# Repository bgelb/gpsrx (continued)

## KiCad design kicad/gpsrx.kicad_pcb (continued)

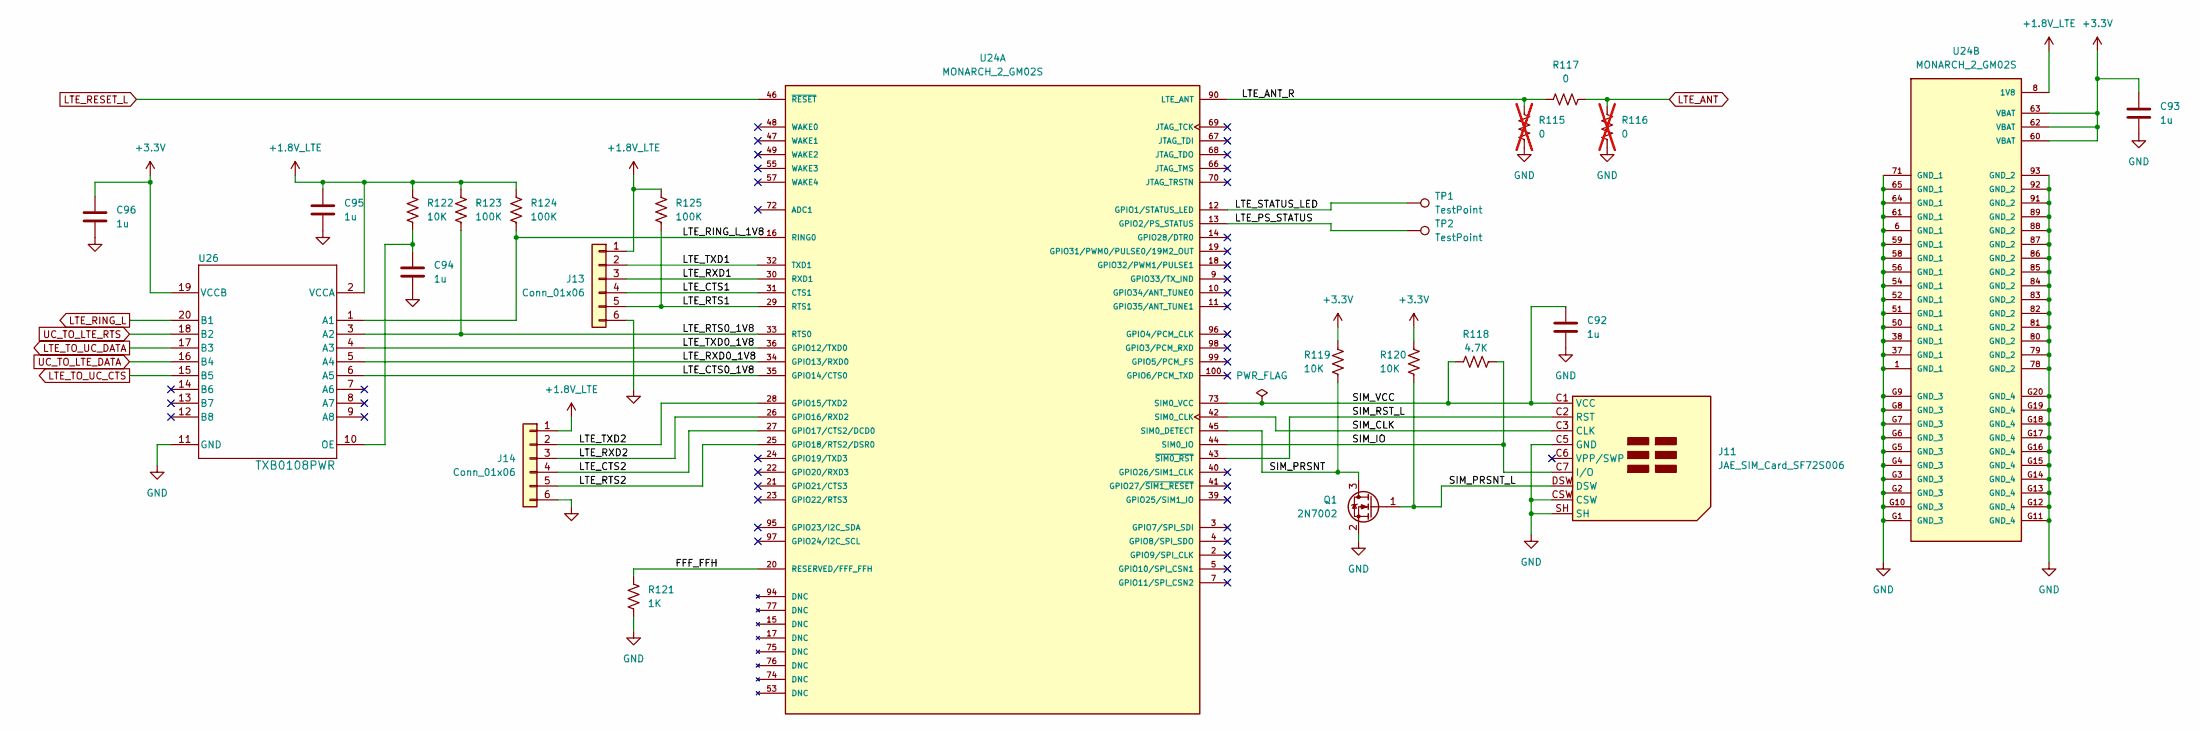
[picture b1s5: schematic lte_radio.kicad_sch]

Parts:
C92, C93, C94, C95, C96: 1u; C_0603_1608Metric_Pad1.08x0.95mm_HandSolder
J11: JAE_SIM_Card_SF72S006
J13, J14: Conn_01x06; PinSocket_1x06_P2.54mm_Vertical
Q1: 2N7002; SOT-23
R115, R116: 0; R_0603_1608Metric_Pad0.98x0.95mm_HandSolder; not fitted
R117: 0; R_0603_1608Metric_Pad0.98x0.95mm_HandSolder
R118: 4.7K; R_0603_1608Metric_Pad0.98x0.95mm_HandSolder
R119, R120, R122: 10K; R_0603_1608Metric_Pad0.98x0.95mm_HandSolder
R121: 1K; R_0603_1608Metric_Pad0.98x0.95mm_HandSolder
R123, R124, R125: 100K; R_0603_1608Metric_Pad0.98x0.95mm_HandSolder
TP1, TP2: TestPoint; TestPoint_Pad_D1.0mm
U24: MONARCH_2_GM02S; XCVR_MONARCH_2_GM02S; PARTREV 11
U26: TXB0108PWR; PW0020A_N

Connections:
/LTE Radio/FFF_FFH: R121.1, U24.20 (RESERVED/FFF_FFH)
/LTE Radio/LTE_ANT_R: R115.1, R117.1, U24.90 (LTE_ANT)
/LTE Radio/LTE_CTS0_1V8: U24.35 (GPIO14/CTS0), U26.6 (A5)
/LTE Radio/LTE_CTS1: J13.4, U24.31 (CTS1)
/LTE Radio/LTE_CTS2: J14.4, U24.27 (GPIO17/CTS2/DCD0)
/LTE Radio/LTE_PS_STATUS: TP2.1, U24.13 (GPIO2/PS_STATUS)
/LTE Radio/LTE_RING_L_1V8: R124.2, U24.16 (RING0), U26.1 (A1)
/LTE Radio/LTE_RTS0_1V8: R123.2, U24.33 (RTS0), U26.3 (A2)
/LTE Radio/LTE_RTS1: J13.5, R125.2, U24.29 (RTS1)
/LTE Radio/LTE_RTS2: J14.5, U24.25 (GPIO18/RTS2/DSR0)
/LTE Radio/LTE_RXD0_1V8: U24.34 (GPIO13/RXD0), U26.5 (A4)
/LTE Radio/LTE_RXD1: J13.3, U24.30 (RXD1)
/LTE Radio/LTE_RXD2: J14.3, U24.26 (GPIO16/RXD2)
/LTE Radio/LTE_STATUS_LED: TP1.1, U24.12 (GPIO1/STATUS_LED)
/LTE Radio/LTE_TXD0_1V8: U24.36 (GPIO12/TXD0), U26.4 (A3)
/LTE Radio/LTE_TXD1: J13.2, U24.32 (TXD1)
/LTE Radio/LTE_TXD2: J14.2, U24.28 (GPIO15/TXD2)
/LTE Radio/SIM_CLK: J11.C3 (CLK), U24.42 (SIM0_CLK)
/LTE Radio/SIM_IO: J11.C7 (I/O), R118.2, U24.44 (SIM0_IO)
/LTE Radio/SIM_PRSNT: Q1.3 (D), R119.2, U24.45 (SIM0_DETECT)
/LTE Radio/SIM_PRSNT_L: J11.DSW, Q1.1 (G), R120.2
/LTE Radio/SIM_RST_L: J11.C2 (RST), U24.43 (~SIM0_RST)
/LTE Radio/SIM_VCC: C92.1, J11.C1 (VCC), R118.1, U24.73 (SIM0_VCC)
GND: C92.2, C93.2, C94.2, C95.2, C96.2, J11.C5 (GND), J11.CSW, J11.SH, J13.6, J14.6, Q1.2 (S), R115.2, R116.2, R121.2, U24.1 (GND_1), U24.6 (GND_1), U24.37 (GND_1), U24.38 (GND_1), U24.50 (GND_1), U24.51 (GND_1), U24.52 (GND_1), U24.54 (GND_1), U24.56 (GND_1), U24.58 (GND_1), U24.59 (GND_1), U24.61 (GND_1), U24.64 (GND_1), U24.65 (GND_1), U24.71 (GND_1), U24.78 (GND_2), U24.79 (GND_2), U24.80 (GND_2), U24.81 (GND_2), U24.82 (GND_2), U24.83 (GND_2), U24.84 (GND_2), U24.85 (GND_2), U24.86 (GND_2), U24.87 (GND_2), U24.88 (GND_2), U24.89 (GND_2), U24.91 (GND_2), U24.92 (GND_2), U24.93 (GND_2), U24.G1 (GND_3), U24.G2 (GND_3), U24.G3 (GND_3), U24.G4 (GND_3), U24.G5 (GND_3), U24.G6 (GND_3), U24.G7 (GND_3), U24.G8 (GND_3), U24.G9 (GND_3), U24.G10 (GND_3), U24.G11 (GND_4), U24.G12 (GND_4), U24.G13 (GND_4), U24.G14 (GND_4), U24.G15 (GND_4), U24.G16 (GND_4), U24.G17 (GND_4), U24.G18 (GND_4), U24.G19 (GND_4), U24.G20 (GND_4), U26.11 (GND); also elsewhere on the board
LTE_ANT: R116.1, R117.2; also elsewhere on the board
LTE_RESET_L: U24.46 (~RESET); also elsewhere on the board
LTE_RING_L: U26.20 (B1); also elsewhere on the board
LTE_TO_UC_CTS: U26.15 (B5); also elsewhere on the board
LTE_TO_UC_DATA: U26.17 (B3); also elsewhere on the board
unnamed: C94.1, R122.2, U26.10 (OE)
UC_TO_LTE_DATA: U26.16 (B4); also elsewhere on the board
UC_TO_LTE_RTS: U26.18 (B2); also elsewhere on the board

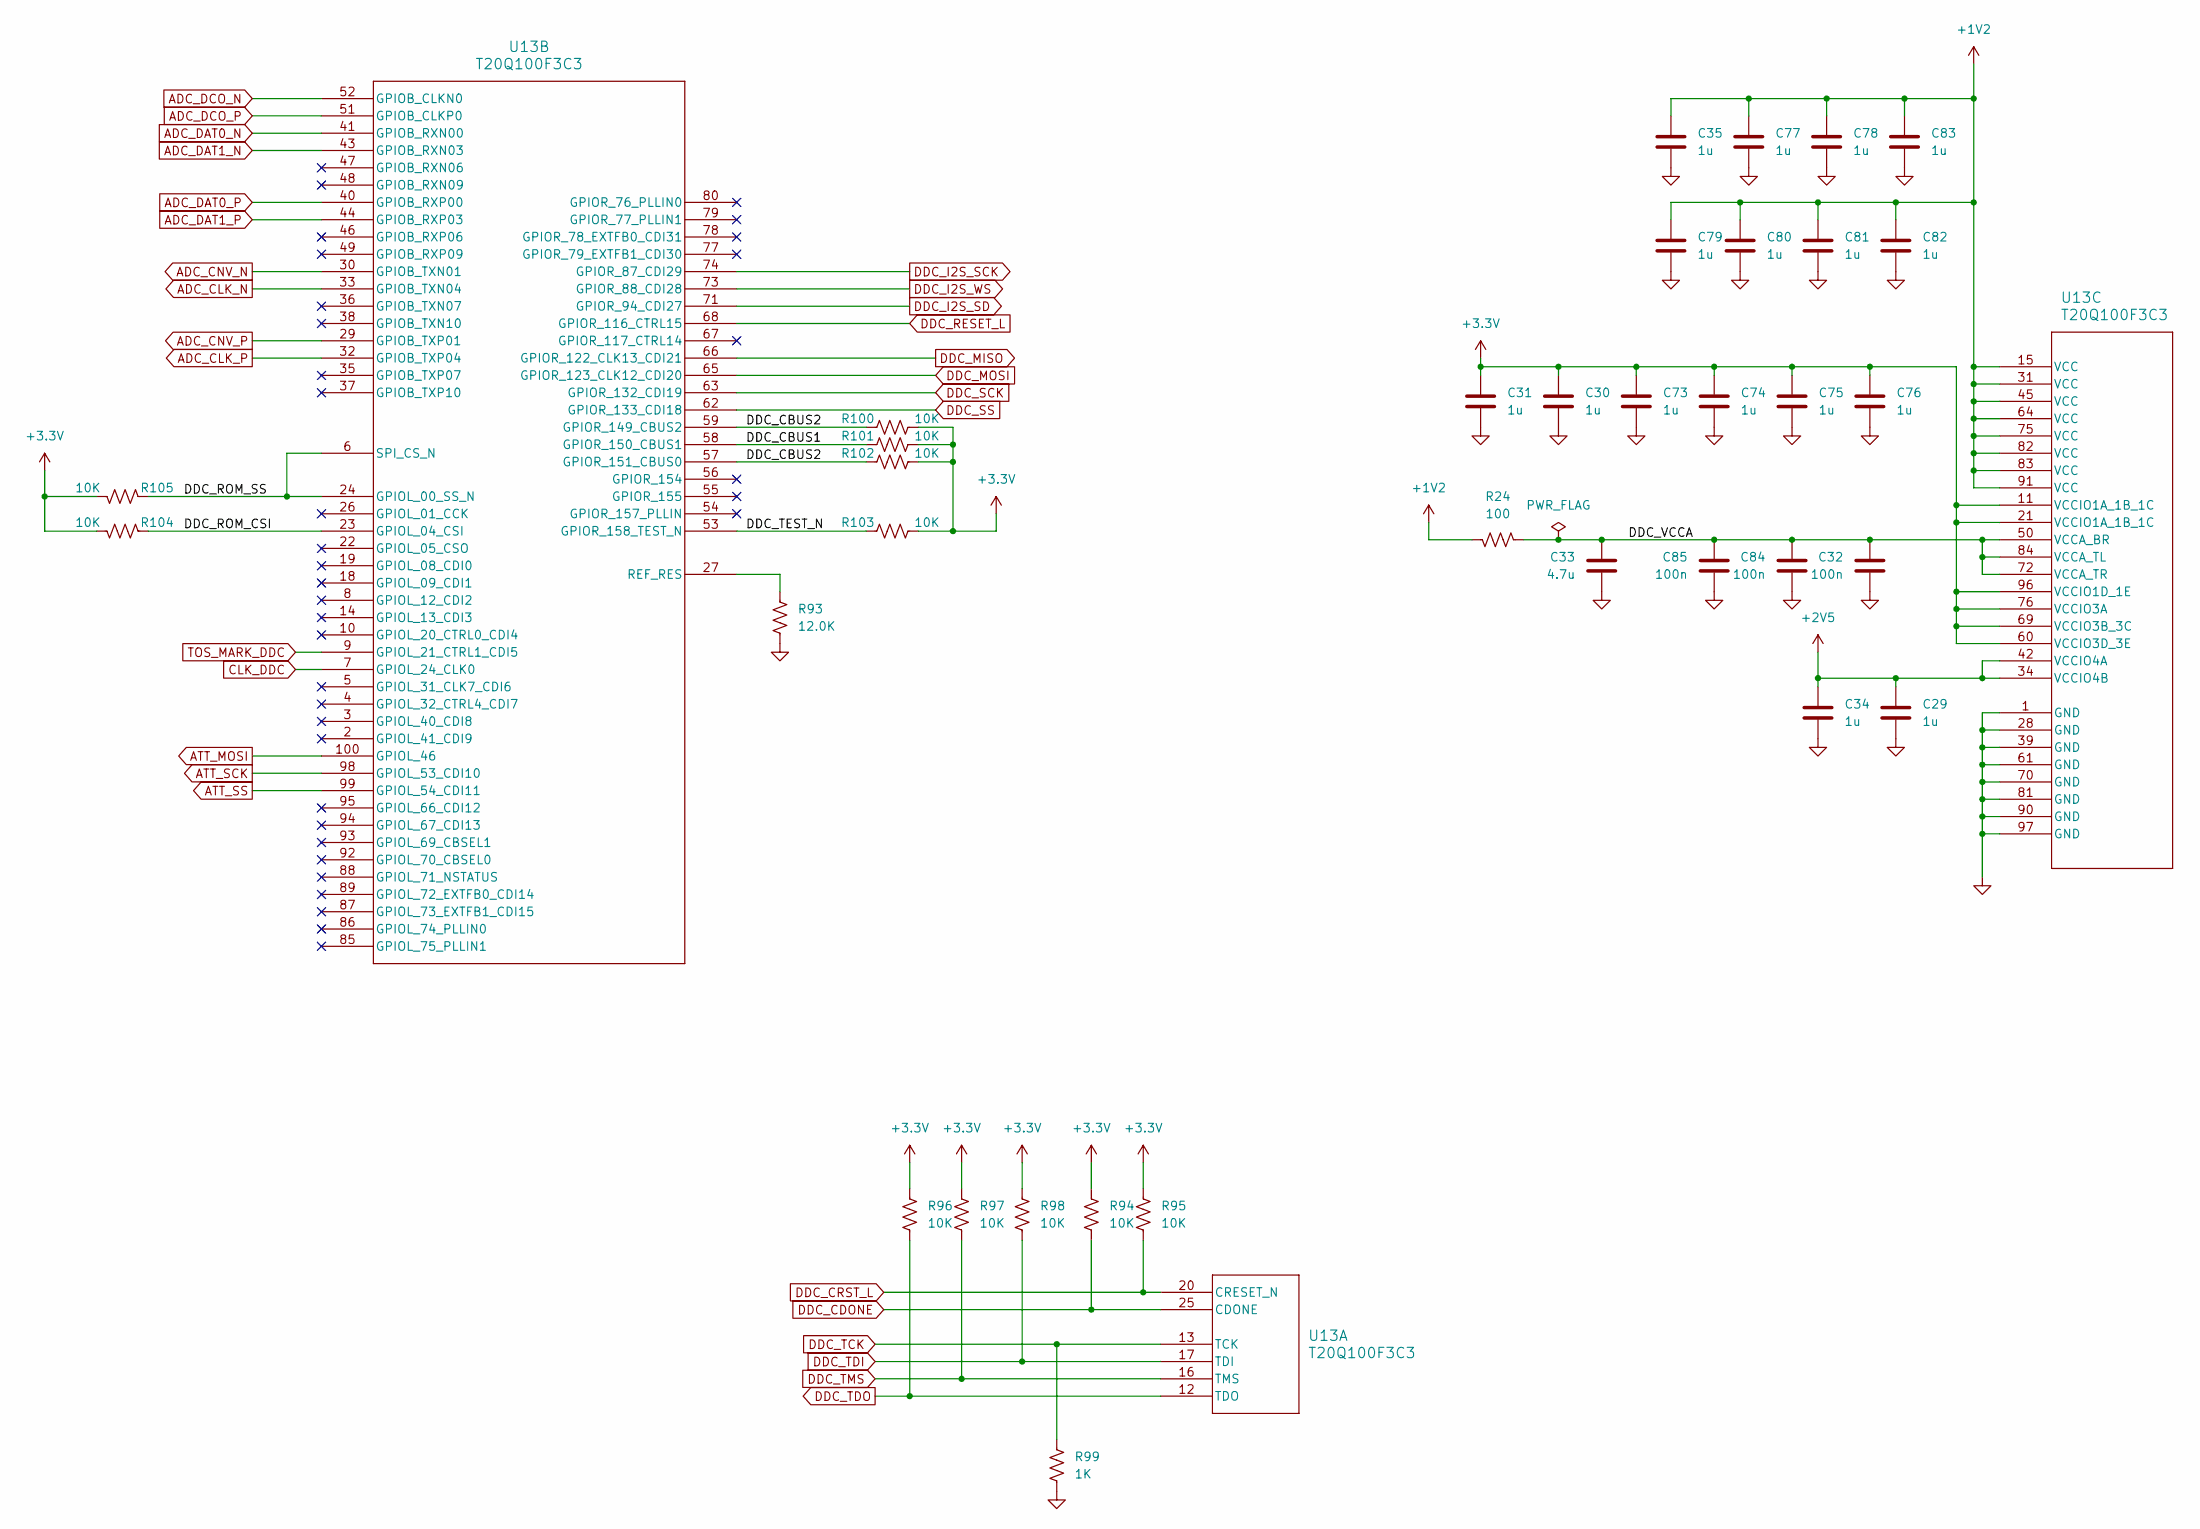
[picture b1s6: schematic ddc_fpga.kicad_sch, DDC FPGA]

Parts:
C29, C30, C31, C34, C35, C73, C74, C75, C76, C77, C78, C79, C80, C81, C82, C83: 1u; C_0603_1608Metric_Pad1.08x0.95mm_HandSolder
C32, C84, C85: 100n; C_0603_1608Metric_Pad1.08x0.95mm_HandSolder
C33: 4.7u; C_0603_1608Metric_Pad1.08x0.95mm_HandSolder
R24: 100; R_0603_1608Metric_Pad0.98x0.95mm_HandSolder
R93: 12.0K; R_0603_1608Metric_Pad0.98x0.95mm_HandSolder
R94, R95, R96, R97, R98, R100, R101, R102, R103, R104, R105: 10K; R_0603_1608Metric_Pad0.98x0.95mm_HandSolder
R99: 1K; R_0603_1608Metric_Pad0.98x0.95mm_HandSolder
U13: T20Q100F3C3; LQFP100_TRION_EFI

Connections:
+1V2: C35.1, C77.1, C78.1, C79.1, C80.1, C81.1, C82.1, C83.1, R24.2, U13.15 (VCC), U13.31 (VCC), U13.45 (VCC), U13.64 (VCC), U13.75 (VCC), U13.82 (VCC), U13.83 (VCC), U13.91 (VCC); also elsewhere on the board
+2V5: C29.1, C34.1, U13.34 (VCCIO4B), U13.42 (VCCIO4A); also elsewhere on the board
/DDC FPGA/DDC_CBUS1: R101.1, U13.58 (GPIOR_150_CBUS1)
/DDC FPGA/DDC_CBUS2: R100.1, R102.1, U13.57 (GPIOR_151_CBUS0), U13.59 (GPIOR_149_CBUS2)
/DDC FPGA/DDC_ROM_CSI: R104.1, U13.23 (GPIOL_04_CSI)
/DDC FPGA/DDC_ROM_SS: R105.1, U13.6 (SPI_CS_N), U13.24 (GPIOL_00_SS_N)
/DDC FPGA/DDC_TEST_N: R103.1, U13.53 (GPIOR_158_TEST_N)
/DDC FPGA/DDC_VCCA: C32.1, C33.1, C84.1, C85.1, R24.1, U13.50 (VCCA_BR), U13.72 (VCCA_TR), U13.84 (VCCA_TL)
ADC_CLK_N: U13.33 (GPIOB_TXN04); also elsewhere on the board
ADC_CLK_P: U13.32 (GPIOB_TXP04); also elsewhere on the board
ADC_CNV_N: U13.30 (GPIOB_TXN01); also elsewhere on the board
ADC_CNV_P: U13.29 (GPIOB_TXP01); also elsewhere on the board
ADC_DAT0_N: U13.41 (GPIOB_RXN00); also elsewhere on the board
ADC_DAT0_P: U13.40 (GPIOB_RXP00); also elsewhere on the board
ADC_DAT1_N: U13.43 (GPIOB_RXN03); also elsewhere on the board
ADC_DAT1_P: U13.44 (GPIOB_RXP03); also elsewhere on the board
ADC_DCO_N: U13.52 (GPIOB_CLKN0); also elsewhere on the board
ADC_DCO_P: U13.51 (GPIOB_CLKP0); also elsewhere on the board
ATT_MOSI: U13.100 (GPIOL_46); also elsewhere on the board
ATT_SCK: U13.98 (GPIOL_53_CDI10); also elsewhere on the board
ATT_SS: U13.99 (GPIOL_54_CDI11); also elsewhere on the board
CLK_DDC: U13.7 (GPIOL_24_CLK0); also elsewhere on the board
DDC_CDONE: R94.2, U13.25 (CDONE); also elsewhere on the board
DDC_CRST_L: R95.2, U13.20 (CRESET_N); also elsewhere on the board
DDC_I2S_SCK: U13.74 (GPIOR_87_CDI29); also elsewhere on the board
DDC_I2S_SD: U13.71 (GPIOR_94_CDI27); also elsewhere on the board
DDC_I2S_WS: U13.73 (GPIOR_88_CDI28); also elsewhere on the board
DDC_MISO: U13.66 (GPIOR_122_CLK13_CDI21); also elsewhere on the board
DDC_MOSI: U13.65 (GPIOR_123_CLK12_CDI20); also elsewhere on the board
DDC_RESET_L: U13.68 (GPIOR_116_CTRL15); also elsewhere on the board
DDC_SCK: U13.63 (GPIOR_132_CDI19); also elsewhere on the board
DDC_SS: U13.62 (GPIOR_133_CDI18); also elsewhere on the board
DDC_TCK: R99.1, U13.13 (TCK); also elsewhere on the board
DDC_TDI: R98.2, U13.17 (TDI); also elsewhere on the board
DDC_TDO: R96.2, U13.12 (TDO); also elsewhere on the board
DDC_TMS: R97.2, U13.16 (TMS); also elsewhere on the board
GND: C29.2, C30.2, C31.2, C32.2, C33.2, C34.2, C35.2, C73.2, C74.2, C75.2, C76.2, C77.2, C78.2, C79.2, C80.2, C81.2, C82.2, C83.2, C84.2, C85.2, R93.2, R99.2, U13.1 (GND), U13.28 (GND), U13.39 (GND), U13.61 (GND), U13.70 (GND), U13.81 (GND), U13.90 (GND), U13.97 (GND); also elsewhere on the board
unnamed: R93.1, U13.27 (REF_RES)
TOS_MARK_DDC: U13.9 (GPIOL_21_CTRL1_CDI5); also elsewhere on the board

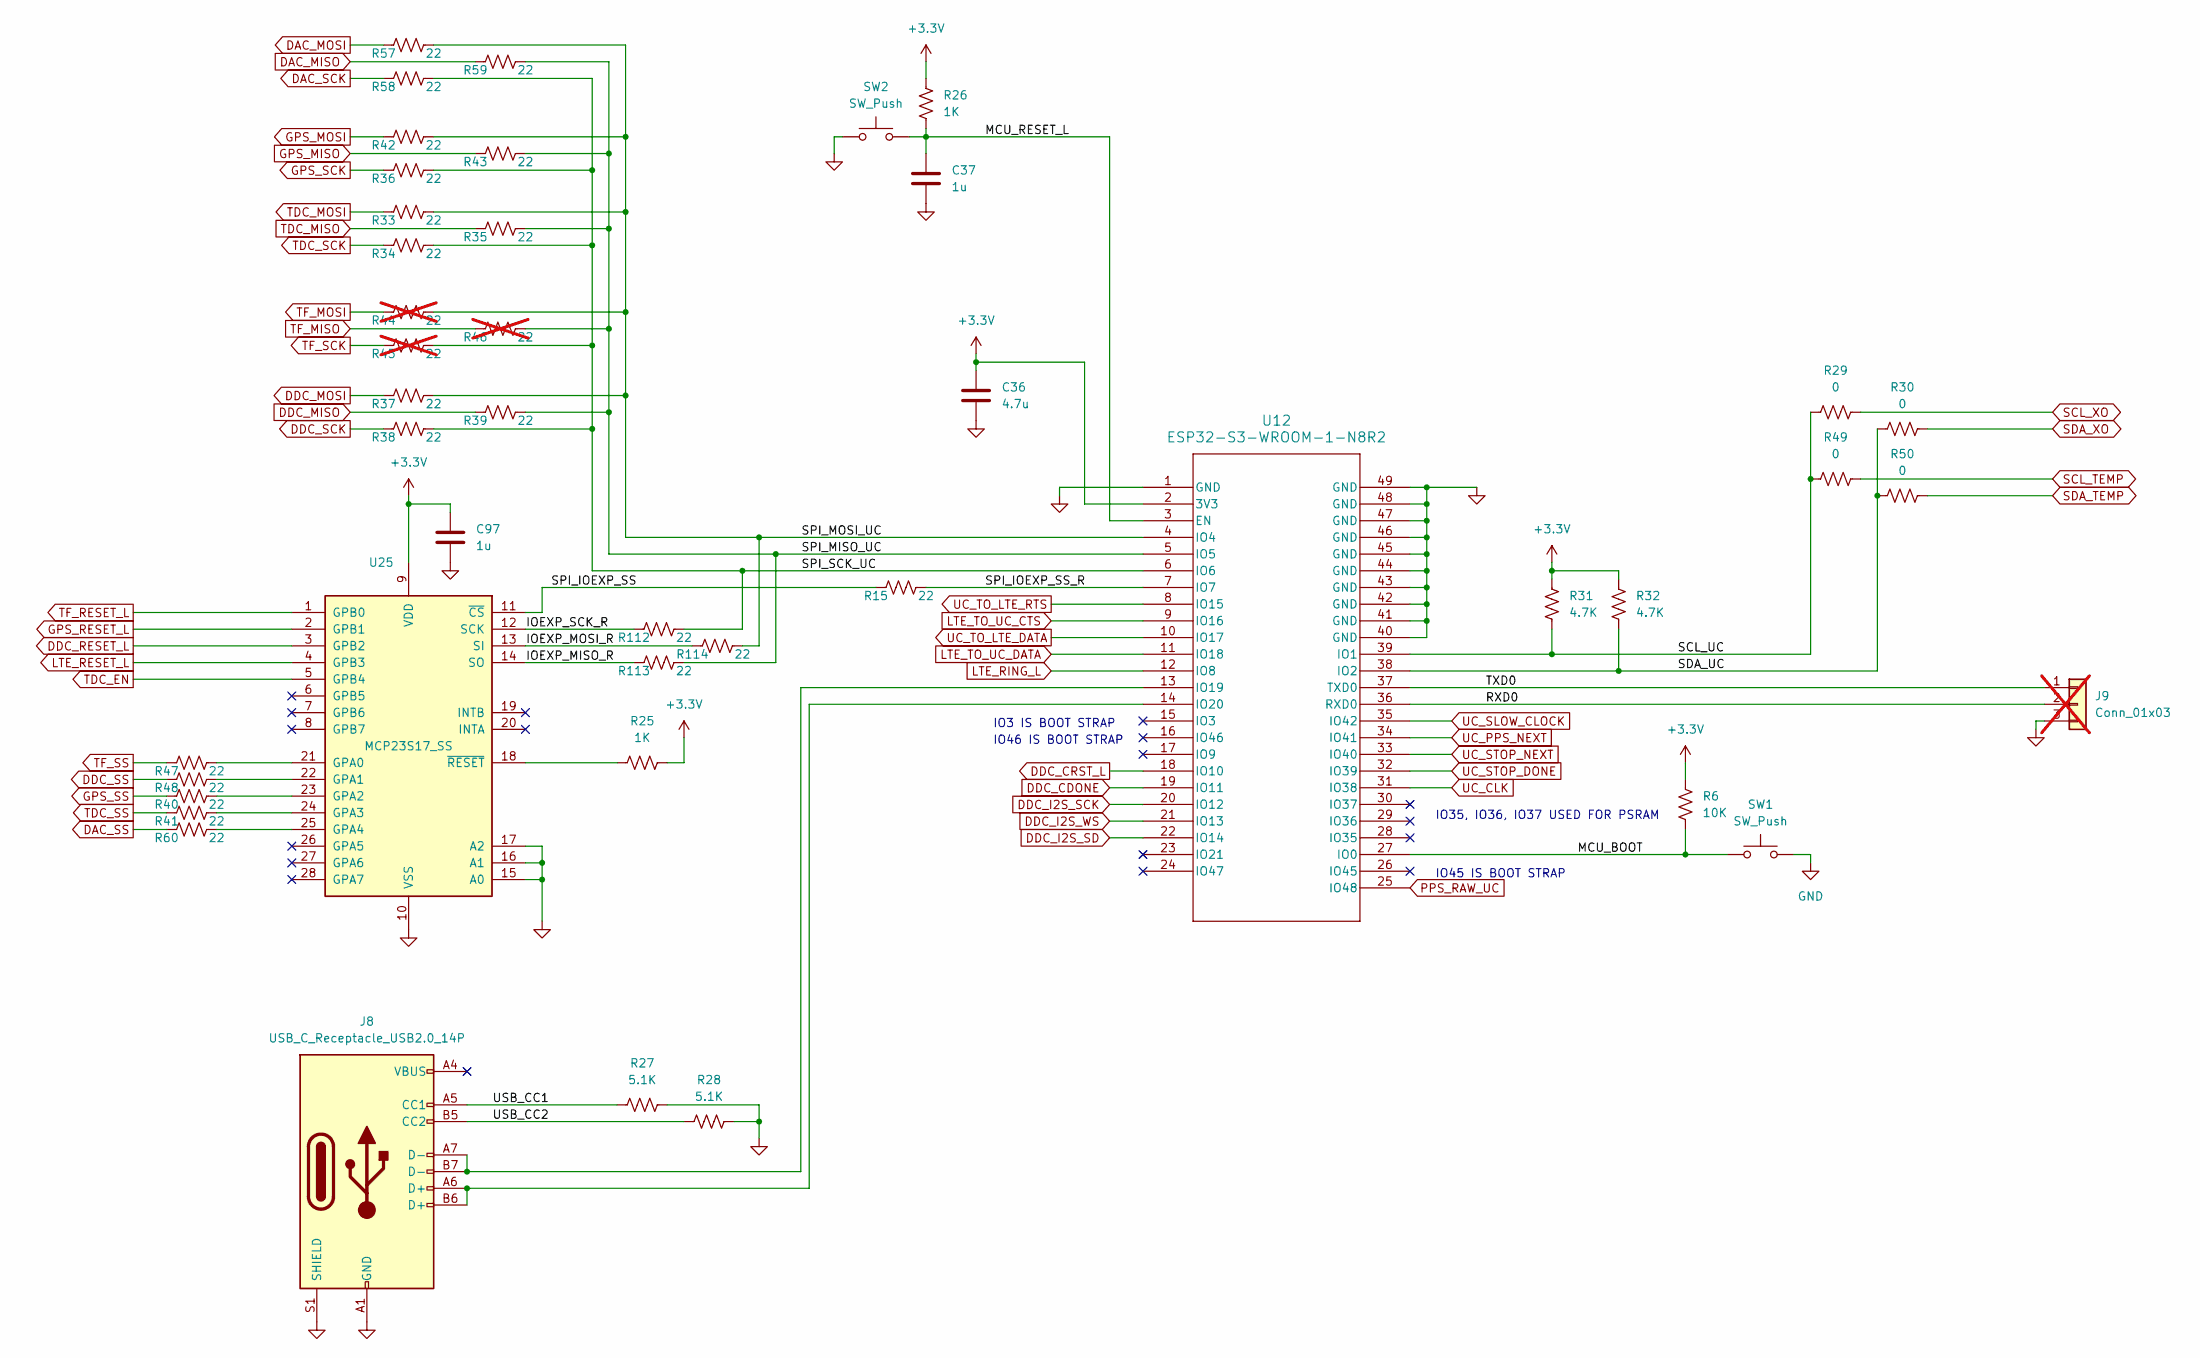
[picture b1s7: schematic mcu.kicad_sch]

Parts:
C36: 4.7u; C_0603_1608Metric_Pad1.08x0.95mm_HandSolder
C37, C97: 1u; C_0603_1608Metric_Pad1.08x0.95mm_HandSolder
J8: USB_C_Receptacle_USB2.0_14P; USB_C_Receptacle_Molex_105450-0101
J9: Conn_01x03; PinHeader_1x03_P2.54mm_Vertical; not fitted
R6: 10K; R_0603_1608Metric_Pad0.98x0.95mm_HandSolder
R15, R33, R34, R35, R36, R37, R38, R39, R40, R41, R42, R43, R47, R48, R57, R58, R59, R60, R112, R113, R114: 22; R_0603_1608Metric_Pad0.98x0.95mm_HandSolder
R25, R26: 1K; R_0603_1608Metric_Pad0.98x0.95mm_HandSolder
R27, R28: 5.1K; R_0603_1608Metric_Pad0.98x0.95mm_HandSolder
R29, R30, R49, R50: 0; R_0603_1608Metric_Pad0.98x0.95mm_HandSolder
R31, R32: 4.7K; R_0603_1608Metric_Pad0.98x0.95mm_HandSolder
R44, R45, R46: 22; R_0603_1608Metric_Pad0.98x0.95mm_HandSolder; not fitted
SW1, SW2: SW_Push; SW_SPST_B3U-1000P
U12: ESP32-S3-WROOM-1-N8R2; ESP32-S3-WROOM-1_EXP
U25: MCP23S17_SS; SSOP-28_5.3x10.2mm_P0.65mm

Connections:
/MCU/IOEXP_MISO_R: R113.1, U25.14 (SO)
/MCU/IOEXP_MOSI_R: R114.1, U25.13 (SI)
/MCU/IOEXP_SCK_R: R112.1, U25.12 (SCK)
/MCU/MCU_BOOT: R6.2, SW1.1, U12.27 (IO0)
/MCU/MCU_RESET_L: C37.1, R26.2, SW2.2, U12.3 (EN)
/MCU/RXD0: J9.2, U12.36 (RXD0)
/MCU/SCL_UC: R29.1, R31.2, R49.1, U12.39 (IO1)
/MCU/SDA_UC: R30.1, R32.2, R50.1, U12.38 (IO2)
/MCU/SPI_IOEXP_SS: R15.1, U25.11 (~CS)
/MCU/SPI_IOEXP_SS_R: R15.2, U12.7 (IO7)
/MCU/SPI_MISO_UC: R35.2, R39.2, R43.2, R46.2, R59.2, R113.2, U12.5 (IO5)
/MCU/SPI_MOSI_UC: R33.2, R37.2, R42.2, R44.2, R57.2, R114.2, U12.4 (IO4)
/MCU/SPI_SCK_UC: R34.2, R36.2, R38.2, R45.2, R58.2, R112.2, U12.6 (IO6)
/MCU/TXD0: J9.1, U12.37 (TXD0)
/MCU/USB_CC1: J8.A5 (CC1), R27.1
/MCU/USB_CC2: J8.B5 (CC2), R28.1
DAC_MISO: R59.1; also elsewhere on the board
DAC_MOSI: R57.1; also elsewhere on the board
DAC_SCK: R58.1; also elsewhere on the board
DAC_SS: R60.2; also elsewhere on the board
DDC_CDONE: U12.19 (IO11); also elsewhere on the board
DDC_CRST_L: U12.18 (IO10); also elsewhere on the board
DDC_I2S_SCK: U12.20 (IO12); also elsewhere on the board
DDC_I2S_SD: U12.22 (IO14); also elsewhere on the board
DDC_I2S_WS: U12.21 (IO13); also elsewhere on the board
DDC_MISO: R39.1; also elsewhere on the board
DDC_MOSI: R37.1; also elsewhere on the board
DDC_RESET_L: U25.3 (GPB2); also elsewhere on the board
DDC_SCK: R38.1; also elsewhere on the board
DDC_SS: R48.1; also elsewhere on the board
GND: C36.2, C37.2, C97.2, J8.A1 (GND), J8.A12 (GND), J8.B1 (GND), J8.B12 (GND), J8.S1 (SHIELD), J9.3, R27.2, R28.2, SW1.2, SW2.1, U12.1 (GND), U12.40 (GND), U12.41 (GND), U12.42 (GND), U12.43 (GND), U12.44 (GND), U12.45 (GND), U12.46 (GND), U12.47 (GND), U12.48 (GND), U12.49 (GND), U25.10 (VSS), U25.15 (A0), U25.16 (A1), U25.17 (A2); also elsewhere on the board
GPS_MISO: R43.1; also elsewhere on the board
GPS_MOSI: R42.1; also elsewhere on the board
GPS_RESET_L: U25.2 (GPB1); also elsewhere on the board
GPS_SCK: R36.1; also elsewhere on the board
GPS_SS: R40.1; also elsewhere on the board
LTE_RESET_L: U25.4 (GPB3); also elsewhere on the board
LTE_RING_L: U12.12 (IO8); also elsewhere on the board
LTE_TO_UC_CTS: U12.9 (IO16); also elsewhere on the board
LTE_TO_UC_DATA: U12.11 (IO18); also elsewhere on the board
unnamed: J8.A7 (D-), J8.B7 (D-), U12.13 (IO19)
unnamed: J8.A6 (D+), J8.B6 (D+), U12.14 (IO20)
unnamed: R47.2, U25.21 (GPA0)
unnamed: R48.2, U25.22 (GPA1)
unnamed: R40.2, U25.23 (GPA2)
unnamed: R41.2, U25.24 (GPA3)
unnamed: R60.1, U25.25 (GPA4)
unnamed: R25.1, U25.18 (~RESET)
PPS_RAW_UC: U12.25 (IO48); also elsewhere on the board
SCL_TEMP: R49.2; also elsewhere on the board
SCL_XO: R29.2; also elsewhere on the board
SDA_TEMP: R50.2; also elsewhere on the board
SDA_XO: R30.2; also elsewhere on the board
TDC_EN: U25.5 (GPB4); also elsewhere on the board
TDC_MISO: R35.1; also elsewhere on the board
TDC_MOSI: R33.1; also elsewhere on the board
TDC_SCK: R34.1; also elsewhere on the board
TDC_SS: R41.1; also elsewhere on the board
TF_MISO: R46.1; also elsewhere on the board
TF_MOSI: R44.1; also elsewhere on the board
TF_RESET_L: U25.1 (GPB0); also elsewhere on the board
TF_SCK: R45.1; also elsewhere on the board
TF_SS: R47.1; also elsewhere on the board
UC_CLK: U12.31 (IO38); also elsewhere on the board
UC_PPS_NEXT: U12.34 (IO41); also elsewhere on the board
UC_SLOW_CLOCK: U12.35 (IO42); also elsewhere on the board
UC_STOP_DONE: U12.32 (IO39); also elsewhere on the board
UC_STOP_NEXT: U12.33 (IO40); also elsewhere on the board
UC_TO_LTE_DATA: U12.10 (IO17); also elsewhere on the board
UC_TO_LTE_RTS: U12.8 (IO15); also elsewhere on the board

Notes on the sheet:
IO3 IS BOOT STRAP
IO35, IO36, IO37 USED FOR PSRAM
IO45 IS BOOT STRAP
IO46 IS BOOT STRAP

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
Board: 6 copper layers, 285 parts (0 on the bottom side), 227 nets, no tracks yet.

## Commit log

2024-02-02 check in working schematic
2024-02-03 add rf
2024-02-03 add files
2024-02-05 wire up mcu
2024-02-07 fix ercs
2024-02-07 more fixes
2024-02-07 fix gnd
2024-02-07 gps bias cap
2024-02-24 bos/tos tweaks
2024-02-24 add tcxo
2024-02-25 add flipflop to stop path
2024-02-29 add flop to pps out
2024-02-29 start timing fpga logic
2024-02-29 work on slow pulse emission
2024-03-02 git ignroe
2024-03-02 first pass done
2024-03-02 elab fixes
2024-03-03 add testbench, fix bugs
2024-03-14 add some frontend stuff
2024-03-15 frontend work
2024-03-16 power and frontend updates
2024-03-16 Tweaks
2024-03-19 new stop_tos_count that outputs pulse train
2024-03-20 add basic quartus project
2024-03-20 move rtl to subdir
2024-03-20 quartus git ignore
2024-03-20 add sdc
2024-03-20 remove rtl from old dir
2024-03-22 async reset
2024-03-22 full constraints
2024-03-28 swap ice40 for max v, add 1.2v switcher
2024-03-28 add max v symbol
2024-03-30 redo uc interface, update sdc and compile settings, timing fixes
2024-03-30 bug fixes
2024-03-30 add triton t20, finish power connections
2024-04-01 add lte radio and various fixes
2024-04-07 assign footprints
2024-04-07 fix pin types in some symbols, gnd->power input
2024-04-09 add net names
2024-04-09 start pcb
2024-04-10 swap txb0108 package, fix pin 65 on cpld
2024-04-11 fix adc_clk, adp7118
2024-04-11 add series term to ioexp_ss_r
2024-05-25 kicad version update
2024-05-25 fix schematic to align w/ pcb
2024-05-27 fix hoel name
2024-05-27 add contractor PCB layout
